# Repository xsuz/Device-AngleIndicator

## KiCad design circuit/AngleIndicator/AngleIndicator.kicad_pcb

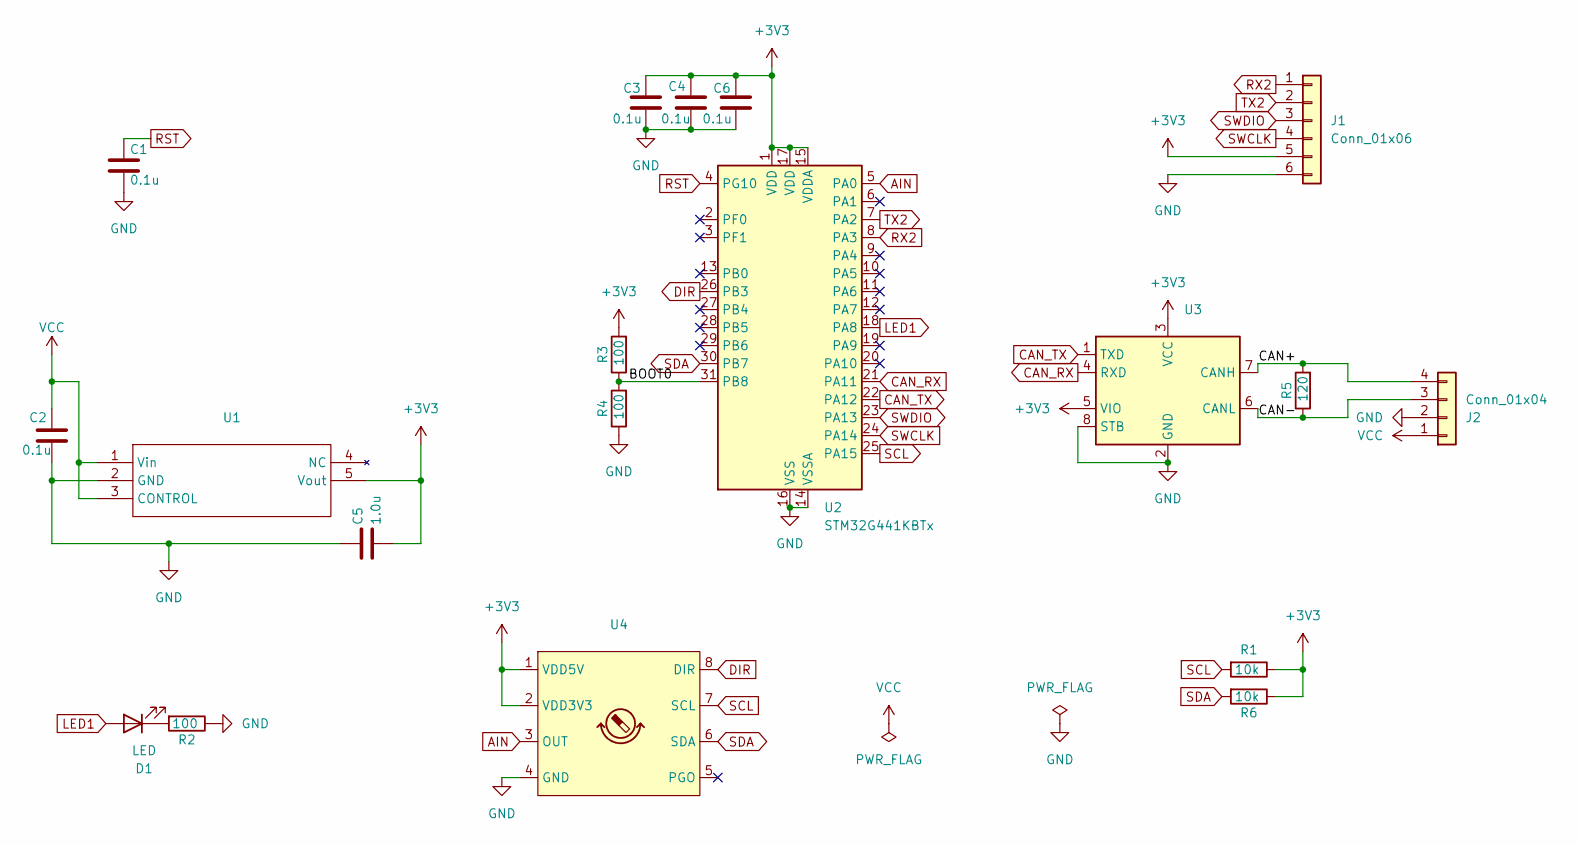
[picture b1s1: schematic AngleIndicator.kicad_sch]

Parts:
C1, C2, C3, C4, C6: 0.1u; C_0603_1608Metric_Pad1.08x0.95mm_HandSolder
C5: 1.0u; C_0603_1608Metric_Pad1.08x0.95mm_HandSolder
D1: LED; D_0603_1608Metric_Pad1.05x0.95mm_HandSolder
J1: Conn_01x06; JST_ZH_B6B-ZR_1x06_P1.50mm_Vertical
J2: Conn_01x04; JST_PH_S4B-PH-K_1x04_P2.00mm_Horizontal
R1, R6: 10k; R_0603_1608Metric_Pad0.98x0.95mm_HandSolder
R2, R3, R4: 100; R_0603_1608Metric_Pad0.98x0.95mm_HandSolder
R5: 120; R_0603_1608Metric_Pad0.98x0.95mm_HandSolder
U1: SOT95P280X130-5N
U2: STM32G441KBTx; LQFP-32_7x7mm_P0.8mm
U3: SOT-23-8_Handsoldering
U4: SOIC-8_3.9x4.9mm_P1.27mm

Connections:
+3V3: C3.1, C4.1, C5.2, C6.1, J1.5, R1.1, R3.2, R6.1, U1.5 (Vout), U2.1 (VDD), U2.15 (VDDA), U2.17 (VDD), U3.3 (VCC), U3.5 (VIO), U4.1 (VDD5V), U4.2 (VDD3V3)
/BOOT0: R3.1, R4.2, U2.31 (PB8)
/CAN+: J2.4, R5.2, U3.7 (CANH)
/CAN-: J2.3, R5.1, U3.6 (CANL)
AIN: U2.5 (PA0), U4.3 (OUT)
CAN_RX: U2.21 (PA11), U3.4 (RXD)
CAN_TX: U2.22 (PA12), U3.1 (TXD)
DIR: U2.26 (PB3), U4.8 (DIR)
GND: C1.2, C2.2, C3.2, C4.2, C5.1, C6.2, J1.6, J2.2, R2.1, R4.1, U1.2 (GND), U2.14 (VSSA), U2.16 (VSS), U2.32 (VSS), U3.2 (GND), U3.8 (STB), U4.4 (GND)
LED1: D1.2 (A), U2.18 (PA8)
unnamed: D1.1 (K), R2.2
RST: C1.1, U2.4 (PG10)
RX2: J1.1, U2.8 (PA3)
SCL: R1.2, U2.25 (PA15), U4.7 (SCL)
SDA: R6.2, U2.30 (PB7), U4.6 (SDA)
SWCLK: J1.4, U2.24 (PA14)
SWDIO: J1.3, U2.23 (PA13)
TX2: J1.2, U2.7 (PA2)
VCC: C2.1, J2.1, U1.1 (Vin), U1.3 (CONTROL)

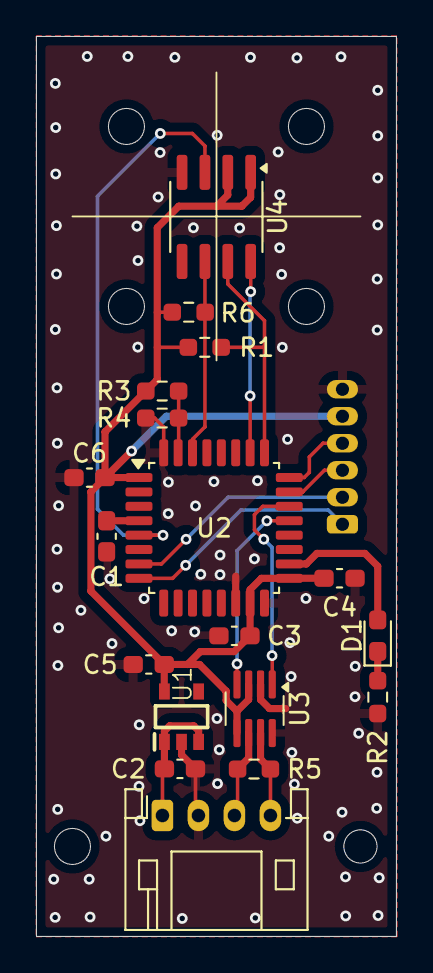
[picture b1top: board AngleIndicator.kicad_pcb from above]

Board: 2 copper layers, 20.0 x 50.0 mm, 19 parts (1 on the bottom side), 19 nets.

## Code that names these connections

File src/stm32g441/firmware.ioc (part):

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Mcu.Name=STM32G441KBTx
Mcu.Package=LQFP32
Mcu.UserName=STM32G441KBTx
PA11.Mode=FDCAN_Activate
PA11.Signal=FDCAN1_RX
PA12.Mode=FDCAN_Activate
PA12.Signal=FDCAN1_TX
PA13.Mode=Serial_Wire
PA13.Signal=SYS_JTMS-SWDIO
PA14.Mode=Serial_Wire
PA14.Signal=SYS_JTCK-SWCLK
PA15.GPIOParameters=GPIO_Speed,GPIO_Pu
PA15.GPIO_Pu=GPIO_PULLUP
PA15.GPIO_Speed=GPIO_SPEED_FREQ_VERY_HIGH
PA15.Mode=I2C
PA15.Signal=I2C1_SCL
PA2.Mode=Asynchronous
PA2.Signal=USART2_TX
PA3.Mode=Asynchronous
PA3.Signal=USART2_RX
PA8.GPIOParameters=GPIO_Label
PA8.GPIO_Label=LED
PA8.Signal=GPIO_Output
PB3.GPIOParameters=GPIO_Label
PB3.GPIO_Label=DIR
PB3.Signal=GPIO_Output
PB7.GPIOParameters=GPIO_Speed,GPIO_Pu
PB7.GPIO_Pu=GPIO_PULLUP
PB7.GPIO_Speed=GPIO_SPEED_FREQ_VERY_HIGH
PB7.Mode=I2C
PB7.Signal=I2C1_SDA
RCC.HSE_VALUE=8000000
RCC.SYSCLKFreq_VALUE=96000000
RCC.SYSCLKSource=RCC_SYSCLKSOURCE_PLLCLK
board=custom

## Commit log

2024-12-09 update Alib
2024-12-10 回路図&PCB追加
2025-01-16 1/09発注分
2025-01-19 pull-up抵抗とアナログ入力を追加
2025-01-19 シルクを更新
2025-01-21 CANコネクタの配置を変更
2025-01-21 stm32g4のプログラム追加
2025-01-21 makefileを追加
2025-01-21 cppに対応
2025-08-26 submoduleを更新 & makefile修正
2025-08-26 FDCANのパラメータをXNaviに合わせた
2025-08-27 clock周波数を下げた & 受信をしないようにして負荷を下げた
2025-08-28 build systemをcmake+ninjaへ移行
2025-08-28 vscodeでのdebugの構成ファイルを追加
